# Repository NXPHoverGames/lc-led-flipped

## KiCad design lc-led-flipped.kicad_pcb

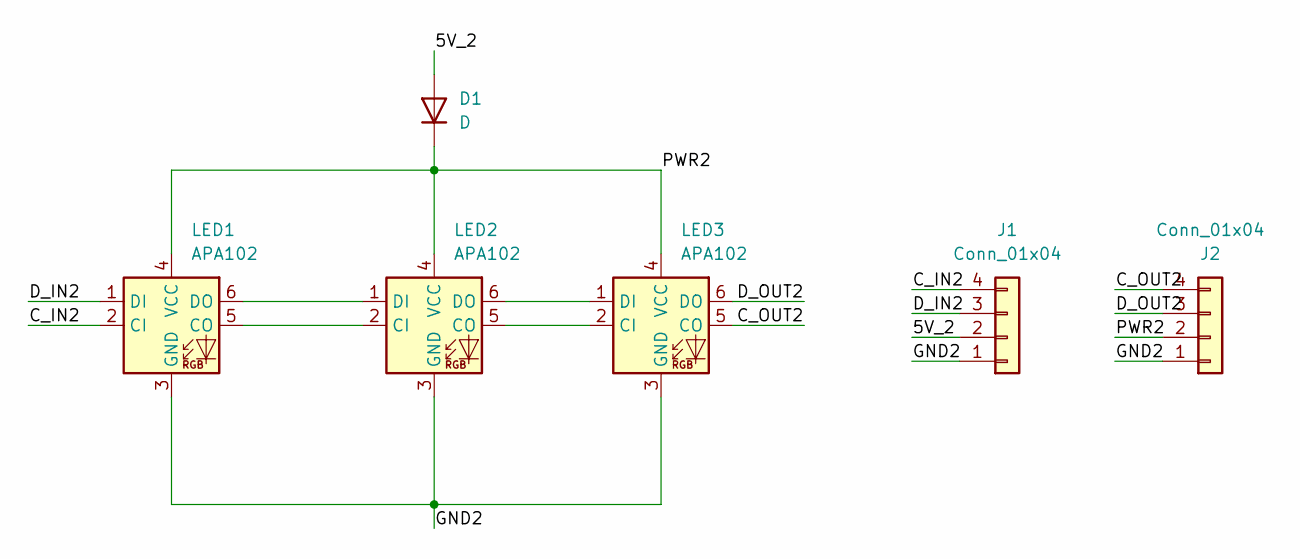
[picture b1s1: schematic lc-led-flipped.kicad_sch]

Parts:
D1: D; D_SOD-123
J1, J2: Conn_01x04; JST_SH_SM04B-SRSS-TB_1x04-1MP_P1.00mm_Horizontal
LED1, LED2, LED3: APA102; LED_RGB_5050-6

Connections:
/5V_2: D1.2 (A), J1.2
/C_IN2: J1.4, LED1.2 (CI)
/C_OUT2: J2.4, LED3.5 (CO)
/D_IN2: J1.3, LED1.1 (DI)
/D_OUT2: J2.3, LED3.6 (DO)
/GND2: J1.1, J1.MP, J2.1, J2.MP, LED1.3 (GND), LED2.3 (GND), LED3.3 (GND)
/PWR2: D1.1 (K), J2.2, LED1.4 (VCC), LED2.4 (VCC), LED3.4 (VCC)
unnamed: LED1.5 (CO), LED2.2 (CI)
unnamed: LED1.6 (DO), LED2.1 (DI)
unnamed: LED2.5 (CO), LED3.2 (CI)
unnamed: LED2.6 (DO), LED3.1 (DI)

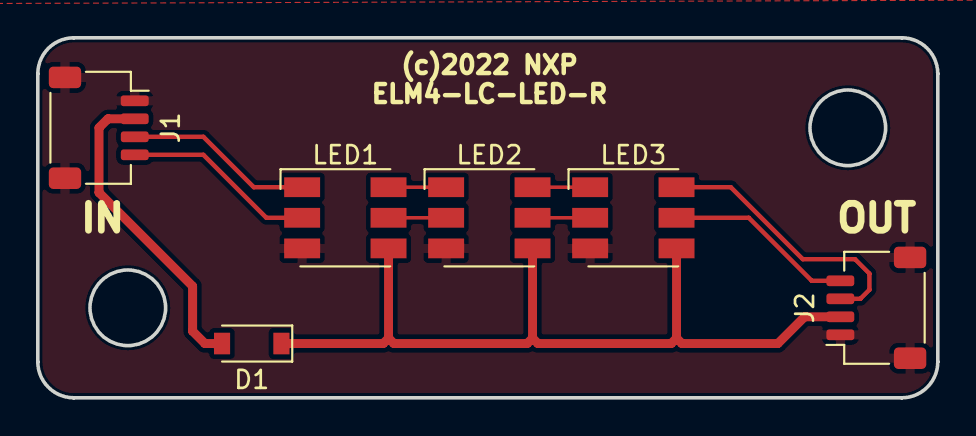
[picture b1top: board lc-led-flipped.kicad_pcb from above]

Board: 2 copper layers, 50.0 x 20.0 mm, 6 parts (0 on the bottom side), 11 nets.

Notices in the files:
lc-led-flipped.kicad_pcb:
(c)2022 NXP
